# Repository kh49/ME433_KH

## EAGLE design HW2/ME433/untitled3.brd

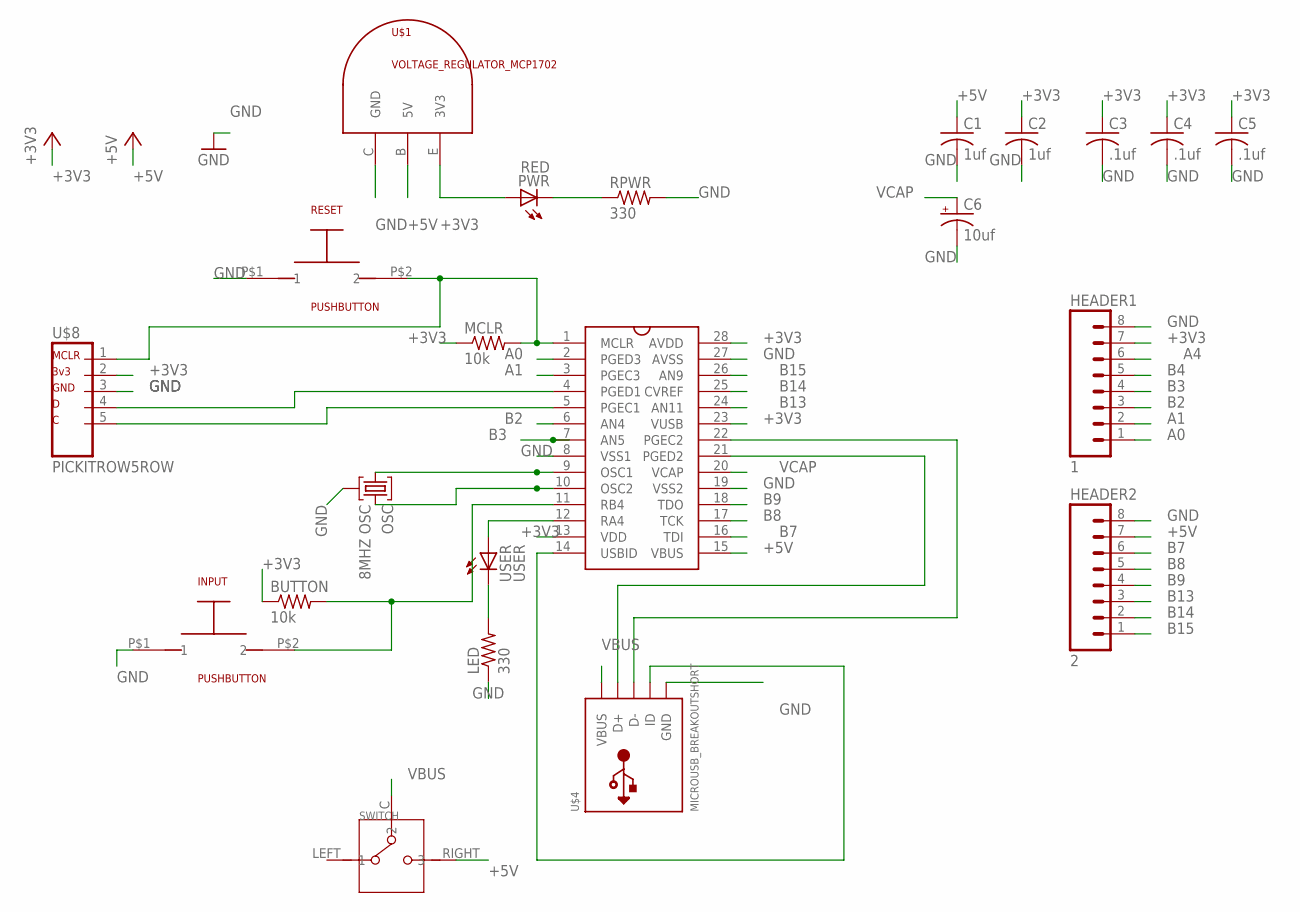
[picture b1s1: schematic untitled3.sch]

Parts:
BUTTON: 10k; 0207/10
C1, C2: 1uf; C025-030X050
C3, C4, C5: .1uf; C025-030X050
C6: 10uf; C025-040X050POL
HEADER1: 1; 1X08_ROUND
HEADER2: 2; 1X08_ROUND
INPUT: PUSHBUTTON
LED: 330; 0207/10
MCLR: 10k; 0207/10
OSC: 8MHZ OSC; CRYSTAL_8MHZ
PWR: RED; LED3MM
RESET: PUSHBUTTON
RPWR: 330; 0207/10
SWITCH: DIP-SLIDE-SWITCH(3P-11.6X4.0X5.4+2.0MM)-EG1218; SW3-2.5-11.6X4.0X5.4+2.0MM
U$1: VOLTAGE_REGULATOR_MCP1702; TO92-EBC
U$4: MICROUSB_BREAKOUTSHORT; USB-MB-SHORT
U$5: PIC32MX250F128B; DIL28-3
U$8: PICKITROW5ROW; 1X05
USER: USER; LED3MM

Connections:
+3V3: BUTTON.1, C2.1, C3.1, C4.1, C5.1, HEADER1.7, MCLR.1, PWR.A, U$1.E (3V3), U$5.13 (VDD), U$5.23 (VUSB), U$5.28 (AVDD), U$8.2 (3V3)
+5V: C1.1, HEADER2.7, SWITCH.RIGHT (3), U$1.B (5V), U$5.15 (VBUS)
A0: HEADER1.1, U$5.2 (PGED3)
A1: HEADER1.2, U$5.3 (PGEC3)
A4: HEADER1.6, U$5.12 (RA4), USER.A
B2: HEADER1.3, U$5.6 (AN4)
B3: HEADER1.4, U$5.7 (AN5)
B4: BUTTON.2, HEADER1.5, INPUT.P$2 (2), U$5.11 (RB4)
B7: HEADER2.6, U$5.16 (TDI)
B8: HEADER2.5, U$5.17 (TCK)
B9: HEADER2.4, U$5.18 (TDO)
B13: HEADER2.3, U$5.24 (AN11)
B14: HEADER2.2, U$5.25 (CVREF)
B15: HEADER2.1, U$5.26 (AN9)
GND: C1.2, C2.2, C3.2, C4.2, C5.2, C6.-, HEADER1.8, HEADER2.8, INPUT.P$1 (1), LED.1, OSC.GND (2), RESET.P$1 (1), RPWR.2, U$1.C (GND), U$4.GND, U$5.8 (VSS1), U$5.19 (VSS2), U$5.27 (AVSS), U$8.3 (GND)
MCLR: MCLR.2, RESET.P$2 (2), U$5.1 (MCLR), U$8.1 (MCLR)
unnamed: LED.2, USER.K (C)
unnamed: PWR.K (C), RPWR.1
OSC1: OSC.OSC1 (1), U$5.9 (OSC1)
OSC2: OSC.OSC2 (3), U$5.10 (OSC2)
PICKITC: U$5.5 (PGEC1), U$8.5 (C)
PICKITD: U$5.4 (PGED1), U$8.4 (D)
USBD+: U$4.D+, U$5.21 (PGED2)
USBD-: U$4.D-, U$5.22 (PGEC2)
USBID: U$4.ID, U$5.14 (USBID)
VBUS: SWITCH.C (2), U$4.VBUS
VCAP: C6.+, U$5.20 (VCAP)

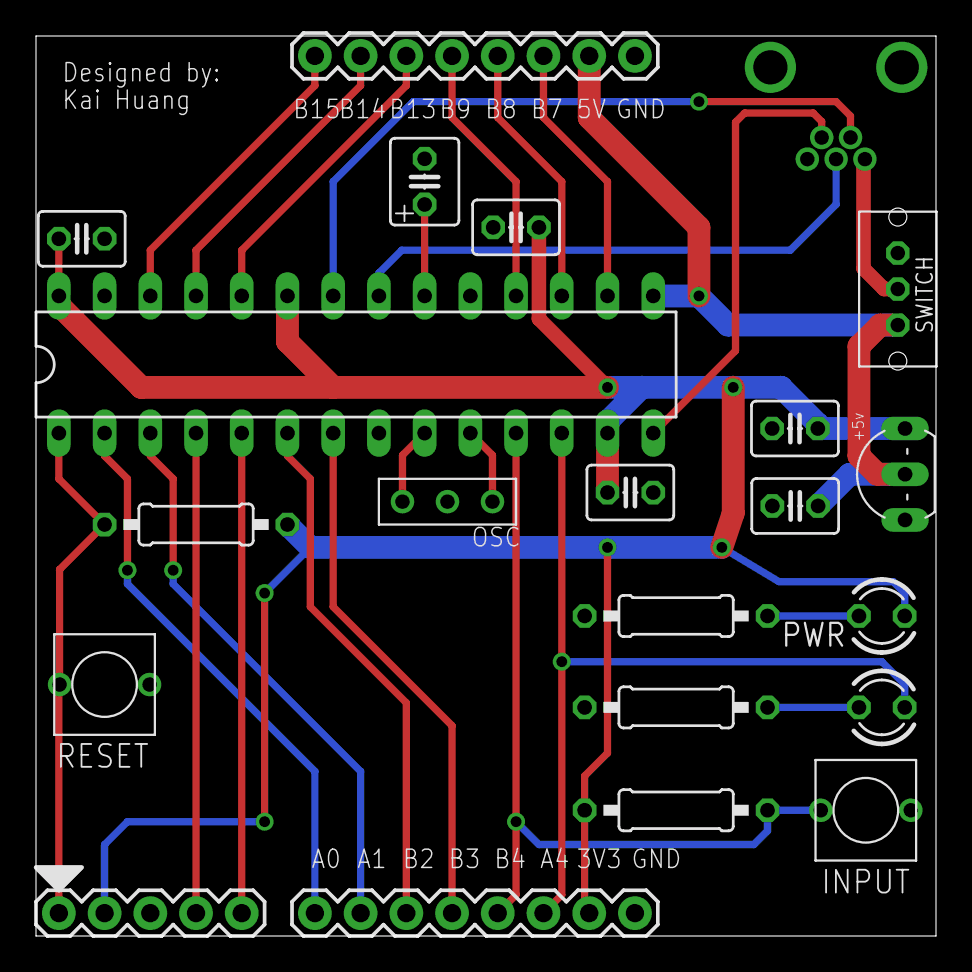
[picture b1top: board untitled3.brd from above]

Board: 2 copper layers, 50.0 x 50.0 mm, 22 parts (0 on the bottom side), 27 nets.

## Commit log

2016-03-31 :confetti_ball: Added .gitattributes & .gitignore files
2016-03-31 HW1 Setup
    initial files for HW1
2016-04-01 DEVCFG 1
    configuration output 48Mhz based on microchip spreadsheet calculator
2016-04-01 include
    include xc.h and added void main()
2016-04-01 Added TRISA setting to set RA4 and RA5 as outputs
    while loop to turn on LED
2016-04-01 Semi-functional delay
    added delay function with counter, PORTAINV function toggles RA4. However, the timing seems to be off by a factor of 10. Timer is only set at 4800 and reaching 1ms bursts
2016-04-01 Delay calibration
    set delay to 4Mhz which seems to be the clock speed with current DEVCFG
2016-04-01 NxR example
    found some sample code
2016-04-01 Plib install
    installed old plib and implemented systemconfigperformance
2016-04-01 Core Timer
    implemented core timer delay set with in delay function for 1000Hz led. Verified on NScope
2016-04-01 Core Timer 2
    doubled frequency so one full light cycle is completed in 1ms isntead of one on or off cycle. added commented code for setting coretimer = 0 although that isn't necessary
2016-04-01 button
    implemented code for button on B4 to hold current LED state on A4. Had to make the button (press = ground)
2016-04-01 Hw1 noise pics
2016-04-01 additional devcfg
    some more stuff added after the template was uploaded. the code to setup wait states and CPU frequency is different
2016-04-03 userid bugfix
    did not designate hex properly
2016-04-04 switch attrib.h
    swapped code from plib.h to attrib.h
2016-04-05 circuit drawing
2016-04-05 final code
2016-04-05 circuit picture
2016-04-10 Eagle
    eagle stuff from this week
2016-04-10 eagle
    check directory
2016-04-10 wide traces
    wider power traces
2016-04-10 rearrange
2016-04-10 completed circuit no error check
2016-04-11 board spacing revision
    got rid of most clearance errors, resized buttons and resonator pin
    width
2016-04-12 presmash
    layout complete, presmash and prenaming
2016-04-12 working gerber
    gerber is workign except for overlap at edge
2016-04-13 fixed gerber edge
    tweaked usb package so gerber doesnt go over edge of pcb
2016-04-13 Ready to be checked before order
    board complete with name and icon
2016-04-13 Ready to be checked before order
    updated voltage regulator package to TO-92 EBC and tweaked power traces
    to avoid drill holes
2016-04-14 Ready to checked before ordering v3
    some more board tweaks, removed redundant via
2016-04-14 Ready to be checked before order
    folder reorganization
2016-04-15 HW4 bugfix
    fixed CS not going low by defining in main.c
2016-04-15 HW4 SPI working
    still need code to make waveforms
2016-04-16 SPI functional
    fixed data transfer errors by making data unsigned so zero casting
    occurred.
2016-04-16 wave generation
    1st try
2016-04-16 spi working sine and triangle on DACa
    DACb does not respond to input
2016-04-18 SPI signal fix
    changed triangle signal to sawtooth. Dacb still doesn't work
2016-04-19 SPI done I2C defined
    SPI is debugged, DacB decays but it does work.
    I2C addresses have all been defined and the functions should work as
    long as actual data bytes are added
2016-04-21 I2C troubleshooting
    had it working for a second. Can't write and can't read now.
2016-04-22 I2c update
    kind of working. code seems functiona, able to read and write to
    registers, however, reading GPIO gets weird results, appears to be noise
    on pins
2016-04-23 i2c still doesn't work
    i2c can read GPIO but doesn't seem to be able to write anything
    correctly, random bits are on
2016-04-23 i2c fixed
    i2c protocol was not followed correctly, had to stop and start to write
    different registers.
    added a 1k resistor to the button input so the voltage drains out. LED
    works
2016-04-23 HW4 complete
    submitted to folder with library functions as well
2016-04-23 HW4 Complete
2016-04-23 WhoamI
    successful whoamI with Imu
2016-04-23 PWM
    pwm on B7 and B8 is functional
2016-04-24 IMU
    multiregister reading is working, probably
    PMW is working but not responding to movement
2016-04-28 gyro kinda works
    multipleread has been fixed, wasn't using a pointer to the array which
    caused the error. something wrong with conversion though
2016-05-04 lcd kinda works
    can't print line of characters yet, can print line of same character
2016-05-04 HW5pt1
    helloworld
2016-05-05 HW 5 and HW6 complete
    fixed IMU data conversion from short to unsigned short, could not just
    typecast, had to add max/2+1 then assign to new unsigned short.
2016-06-10 All HW Complete
